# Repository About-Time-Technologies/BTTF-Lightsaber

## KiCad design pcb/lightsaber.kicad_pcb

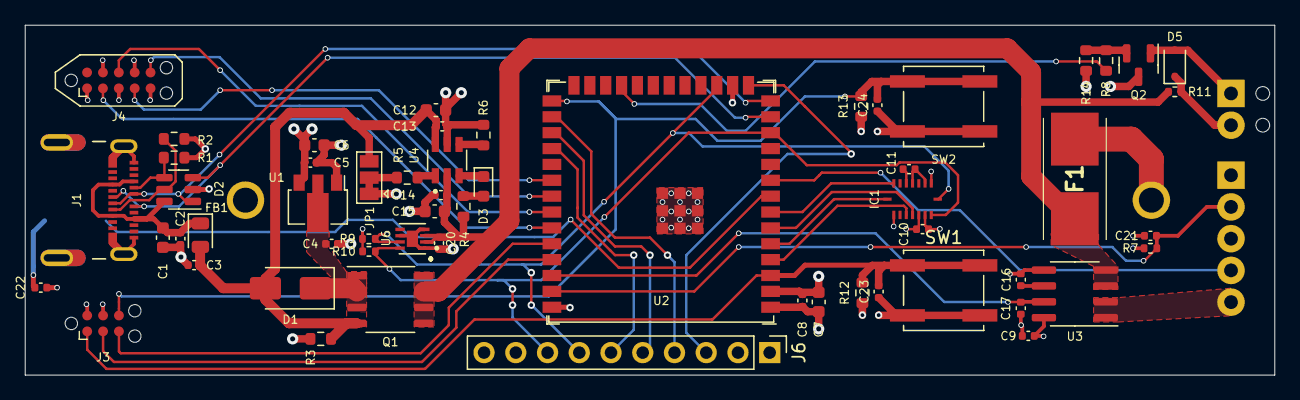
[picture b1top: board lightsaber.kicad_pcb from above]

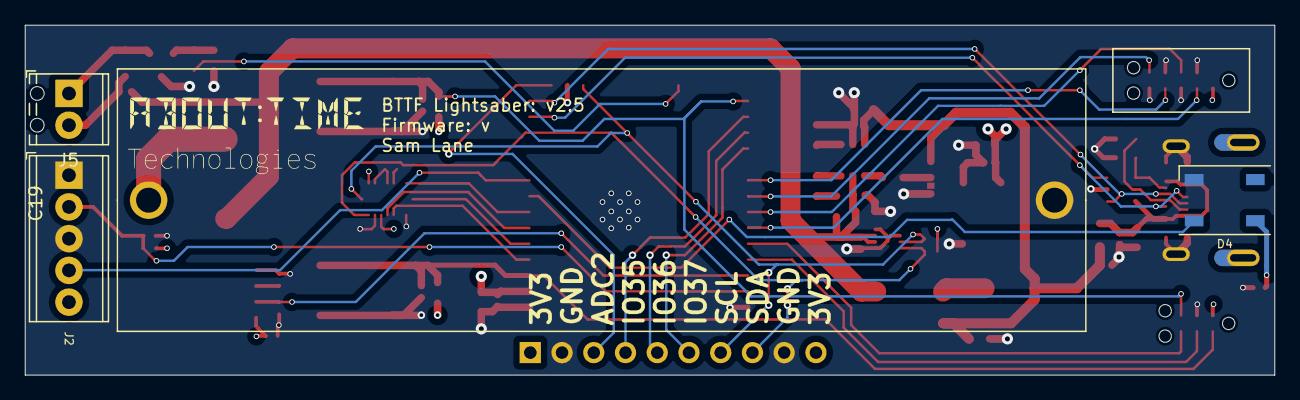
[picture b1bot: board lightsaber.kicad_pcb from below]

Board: 4 copper layers, 100.0 x 28.0 mm, 61 parts (4 on the bottom side), 44 nets.

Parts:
C1, C6, C7, C12, C15: 10uF; C_0603_1608Metric
C2, C4, C5, C8, C13, C14, C21, C22, C23, C24: 1uF; C_0402_1005Metric
C3, C9, C10, C11, C20: 100nF; C_0402_1005Metric
C16: 1nF; C_0402_1005Metric
C17: 4.7nF; C_0402_1005Metric
C19: 18650 Holder; 18650-Holder
D1: Schottky; D_SMA
D2: SP0505BAHT; SOT-23-6
D3: LED; LED_0603_1608Metric
D4: WS2812B; LED_WS2812B_PLCC4_5.0x5.0mm_P3.2mm
D5: 1N4148; D_SOD-323
F1: 8A Fuse; 0154008DR
FB1: FerriteBead; D_0805_2012Metric
IC1: BMI055; QFN50P300X450X100-16N
J1: 2012670005; MOLEX_2012670005
J2: Screw_Terminal_01x05; TerminalBlock_Phoenix_MPT-0,5-5-2.54_1x05_P2.54mm_Horizontal
J3: ESP32 Prog; Tag-Connect_TC2030-IDC-NL_2x03_P1.27mm_Vertical
J4: ESP32 JTAG; Tag-Connect_TC2050-IDC-NL_2x05_P1.27mm_Vertical_with_bottom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
J5: Conn_01x02; TerminalBlock_Phoenix_MPT-0,5-2-2.54_1x02_P2.54mm_Horizontal
J6: Conn_01x10; PinHeader_1x10_P2.54mm_Vertical
JP1: 10k Bridge; SolderJumper-3_P1.3mm_Bridged12_Pad1.0x1.5mm
Q1: PMOS; SSOP-8_3.9x5.05mm_P1.27mm
Q2: NPN; SOT-23
R1, R2: 5.1k; R_0603_1608Metric
R3: 100k; R_0603_1608Metric
R4, R6, R8: 1k; R_0603_1608Metric
R5, R12, R13, R14: 10k; R_0603_1608Metric
R7: 10k; R_0402_1005Metric
R9, R10: 4.7k; R_0402_1005Metric
R11: 10R; R_0402_1005Metric
SW1, SW2: SW_Push; SW_Push_1P1T_NO_CK_KSC6xxJ
U1: ME6211A33PG-N; SOT-89-3
U2: ESP32-S3-WROOM-1; ESP32-S3-WROOM-1U
U3: ACS725xLCTR-10AU; SOIC-8_3.9x4.9mm_P1.27mm
U4: BQ21040DBVR; SOT95P280X145-6N
U6: MAX17048G+T10; SON50P200X200X80-9N

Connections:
+3.3V: C5.2, C6.1, C7.1, C8.2, C9.1, C10.1, C11.1, C22.2, D4.1 (VDD), IC1.3 (VDD), IC1.7 (PS), IC1.11 (VDDIO), J3.2, J4.1, J6.1, J6.10, R7.2, R9.1, R10.1, R12.1, R13.1, U1.3 (VOUT), U2.2 (3V3), U3.8 (VCC)
+BATT: C14.1, C15.1, C20.1, F1.1, Q1.5 (D), Q1.6 (D), Q1.7 (D), Q1.8 (D), R4.1, R11.2, U3.3 (IP-), U3.4 (IP-), U4.2 (OUT), U6.2 (CELL), U6.3 (VDD)
/ACS_FILTER: C16.1, U3.6 (FILTER)
/BAT_FUSE: C19.1 (VBAT), F1.2
/BQ_ISET: R6.1, U4.4 (ISET)
/BQ_TS: R5.2, U4.1 (TS)
/BQ_TS_JUMP: JP1.2 (C), R5.1
/CC1: D2.4 (K), J1.A5 (CC1), R1.1
/CC2: D2.5 (K), J1.B5 (CC2), R2.1
/CHG_LED: D3.1 (K), U4.3 (~CHG)
/CHG_LED_RES: D3.2 (A), R4.2
/MOTOR_NEG: D5.2 (A), J5.1 (Pin_2), Q2.1 (C)
/MOTOR_POS: D5.1 (K), J5.2 (Pin_1), R11.1
/MOTOR_TRANSISTOR: Q2.2 (B), R8.2, R14.2
/VBUS: C1.1, C2.2, D2.6 (K), FB1.1, J1.A4 (VBUS1), J1.A9 (VBUS2), J1.B4 (VBUS3), J1.B9 (VBUS4)
D+: D2.1 (K), J1.A6 (D1+), J1.B6 (D2+), U2.14 (GPIO20/U1CTS/ADC2_CH9/CLK_OUT1/USB_D+)
D-: D2.3 (K), J1.A7 (D1-), J1.B7 (D2-), U2.13 (GPIO19/U1RTS/ADC2_CH8/CLK_OUT2/USB_D-)
ESP32_BMI_ACCEL_1: IC1.12 (INT3), U2.6 (GPIO6/TOUCH6/ADC1_CH5)
ESP32_BMI_ACCEL_2: IC1.13 (INT4), U2.4 (GPIO4/TOUCH4/ADC1_CH3)
ESP32_BMI_GYRO_1: IC1.16 (INT1), U2.5 (GPIO5/TOUCH5/ADC1_CH4)
ESP32_BMI_GYRO_2: IC1.1 (INT2), U2.7 (GPIO7/TOUCH7/ADC1_CH6)
ESP32_EXTERN_ADC: J6.3, U2.15 (GPIO3/TOUCH3/ADC1_CH2)
ESP32_EXTERN_IO35: J6.4, U2.28 (SPIIO6/GPIO35/FSPID/SUBSPID)
ESP32_EXTERN_IO36: J6.5, U2.29 (SPIIO7/GPIO36/FSPICLK/SUBSPICLK)
ESP32_EXTERN_IO37: J6.6, U2.30 (SPIDQS/GPIO37/FSPIQ/SUBSPIQ)
ESP32_I2C_SCL: IC1.8 (SCX), J6.7, R9.2, U2.17 (GPIO9/TOUCH9/ADC1_CH8/FSPIHD/SUBSPIHD), U6.7 (SCL)
ESP32_I2C_SDA: IC1.9 (SDX), J6.8, R10.2, U2.12 (GPIO8/TOUCH8/ADC1_CH7/SUBSPICS1), U6.8 (SDA)
ESP_CURRENT_SENSE: C17.1, U2.38 (GPIO2/TOUCH2/ADC1_CH1), U3.7 (VIOUT)
ESP_EN: C23.2, J3.1, R12.2, SW1.2, U2.3 (EN)
ESP_IO0: C24.2, J3.6, R13.2, SW2.1, U2.27 (GPIO0/BOOT)
ESP_LED_DATA: J2.4, U2.9 (GPIO16/U0CTS/ADC2_CH5/XTAL_32K_N)
ESP_LED_DEBUG: D4.4 (DIN), U2.8 (GPIO15/U0RTS/ADC2_CH4/XTAL_32K_P)
ESP_MOTOR: R8.1, U2.23 (GPIO21)
ESP_TCK: J4.4, U2.32 (MTCK/GPIO39/CLK_OUT3/SUBSPICS1)
ESP_TDI: J4.8, U2.34 (MTDI/GPIO41/CLK_OUT1)
ESP_TDO: J4.6, U2.33 (MTDO/GPIO40/CLK_OUT2)
ESP_TMS: J4.2, U2.35 (MTMS/GPIO42)
ESP_UART_RX: J3.5, U2.36 (U0RXD/GPIO44/CLK_OUT2)
ESP_UART_TX: J3.3, U2.37 (U0TXD/GPIO43/CLK_OUT1)
ESP_USER_BUTTON: C21.2, J2.2, R7.1, U2.39 (GPIO1/TOUCH1/ADC1_CH0)
GND: C1.2, C2.1, C3.2, C4.1, C5.1, C6.2, C7.2, C8.1, C9.2, C10.2, C11.2, C12.2, C13.2, C14.2, C15.2, C16.2, C17.2, C19.2 (GND), C20.2, C21.1, C22.1, C23.1, C24.1, D2.2 (A), D4.3 (VSS), IC1.4 (GNDA), IC1.6 (GNDIO), IC1.10 (SDO2), IC1.15 (SDO1), J1.A1 (GND1), J1.A12 (GND2), J1.B1 (GND3), J1.B12 (GND4), J1.S1 (SHIELD), J1.S2 (SHIELD), J1.S3 (SHIELD), J1.S4 (SHIELD), J2.1, J2.3, J3.4, J4.3, J4.5, J4.7, J4.9, J6.2, J6.9, JP1.1 (A), Q2.3 (E), R1.2, R2.2, R3.2, R6.2, R14.1, SW1.1, SW2.2, U1.1 (GND), U2.1 (GND), U2.16 (GPIO46), U2.40 (GND), U2.41 (GND), U3.5 (GND), U4.5 (GND), U6.1 (CTG), U6.4 (GND), U6.6 (QSTRT), U6.9 (EP)
LED_PWR: J2.5, U3.1 (IP+), U3.2 (IP+)
VCC: C4.2, D1.1 (K), Q1.1 (S), Q1.2 (S), Q1.3 (S), U1.2 (VIN)
VDD: C3.1, C12.1, C13.1, D1.2 (A), FB1.2, JP1.3 (B), Q1.4 (G), R3.1, U4.6 (VIN)

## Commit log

2023-07-15 Initial PCB design and rough layout
2023-07-20 Adding multiverse
2023-07-20 Initial routing
2023-07-24 Fuses and current detection
2023-07-29 General tidyup
2023-08-04 Pre-review
2023-08-04 ERC Complete
2023-08-04 Laptop footprints
2023-08-04 All symbols imported
2023-08-04 Completed design
2023-08-05 Tidying up routing
2023-08-08 Adding external IO
2023-10-11 Tidying up traces
